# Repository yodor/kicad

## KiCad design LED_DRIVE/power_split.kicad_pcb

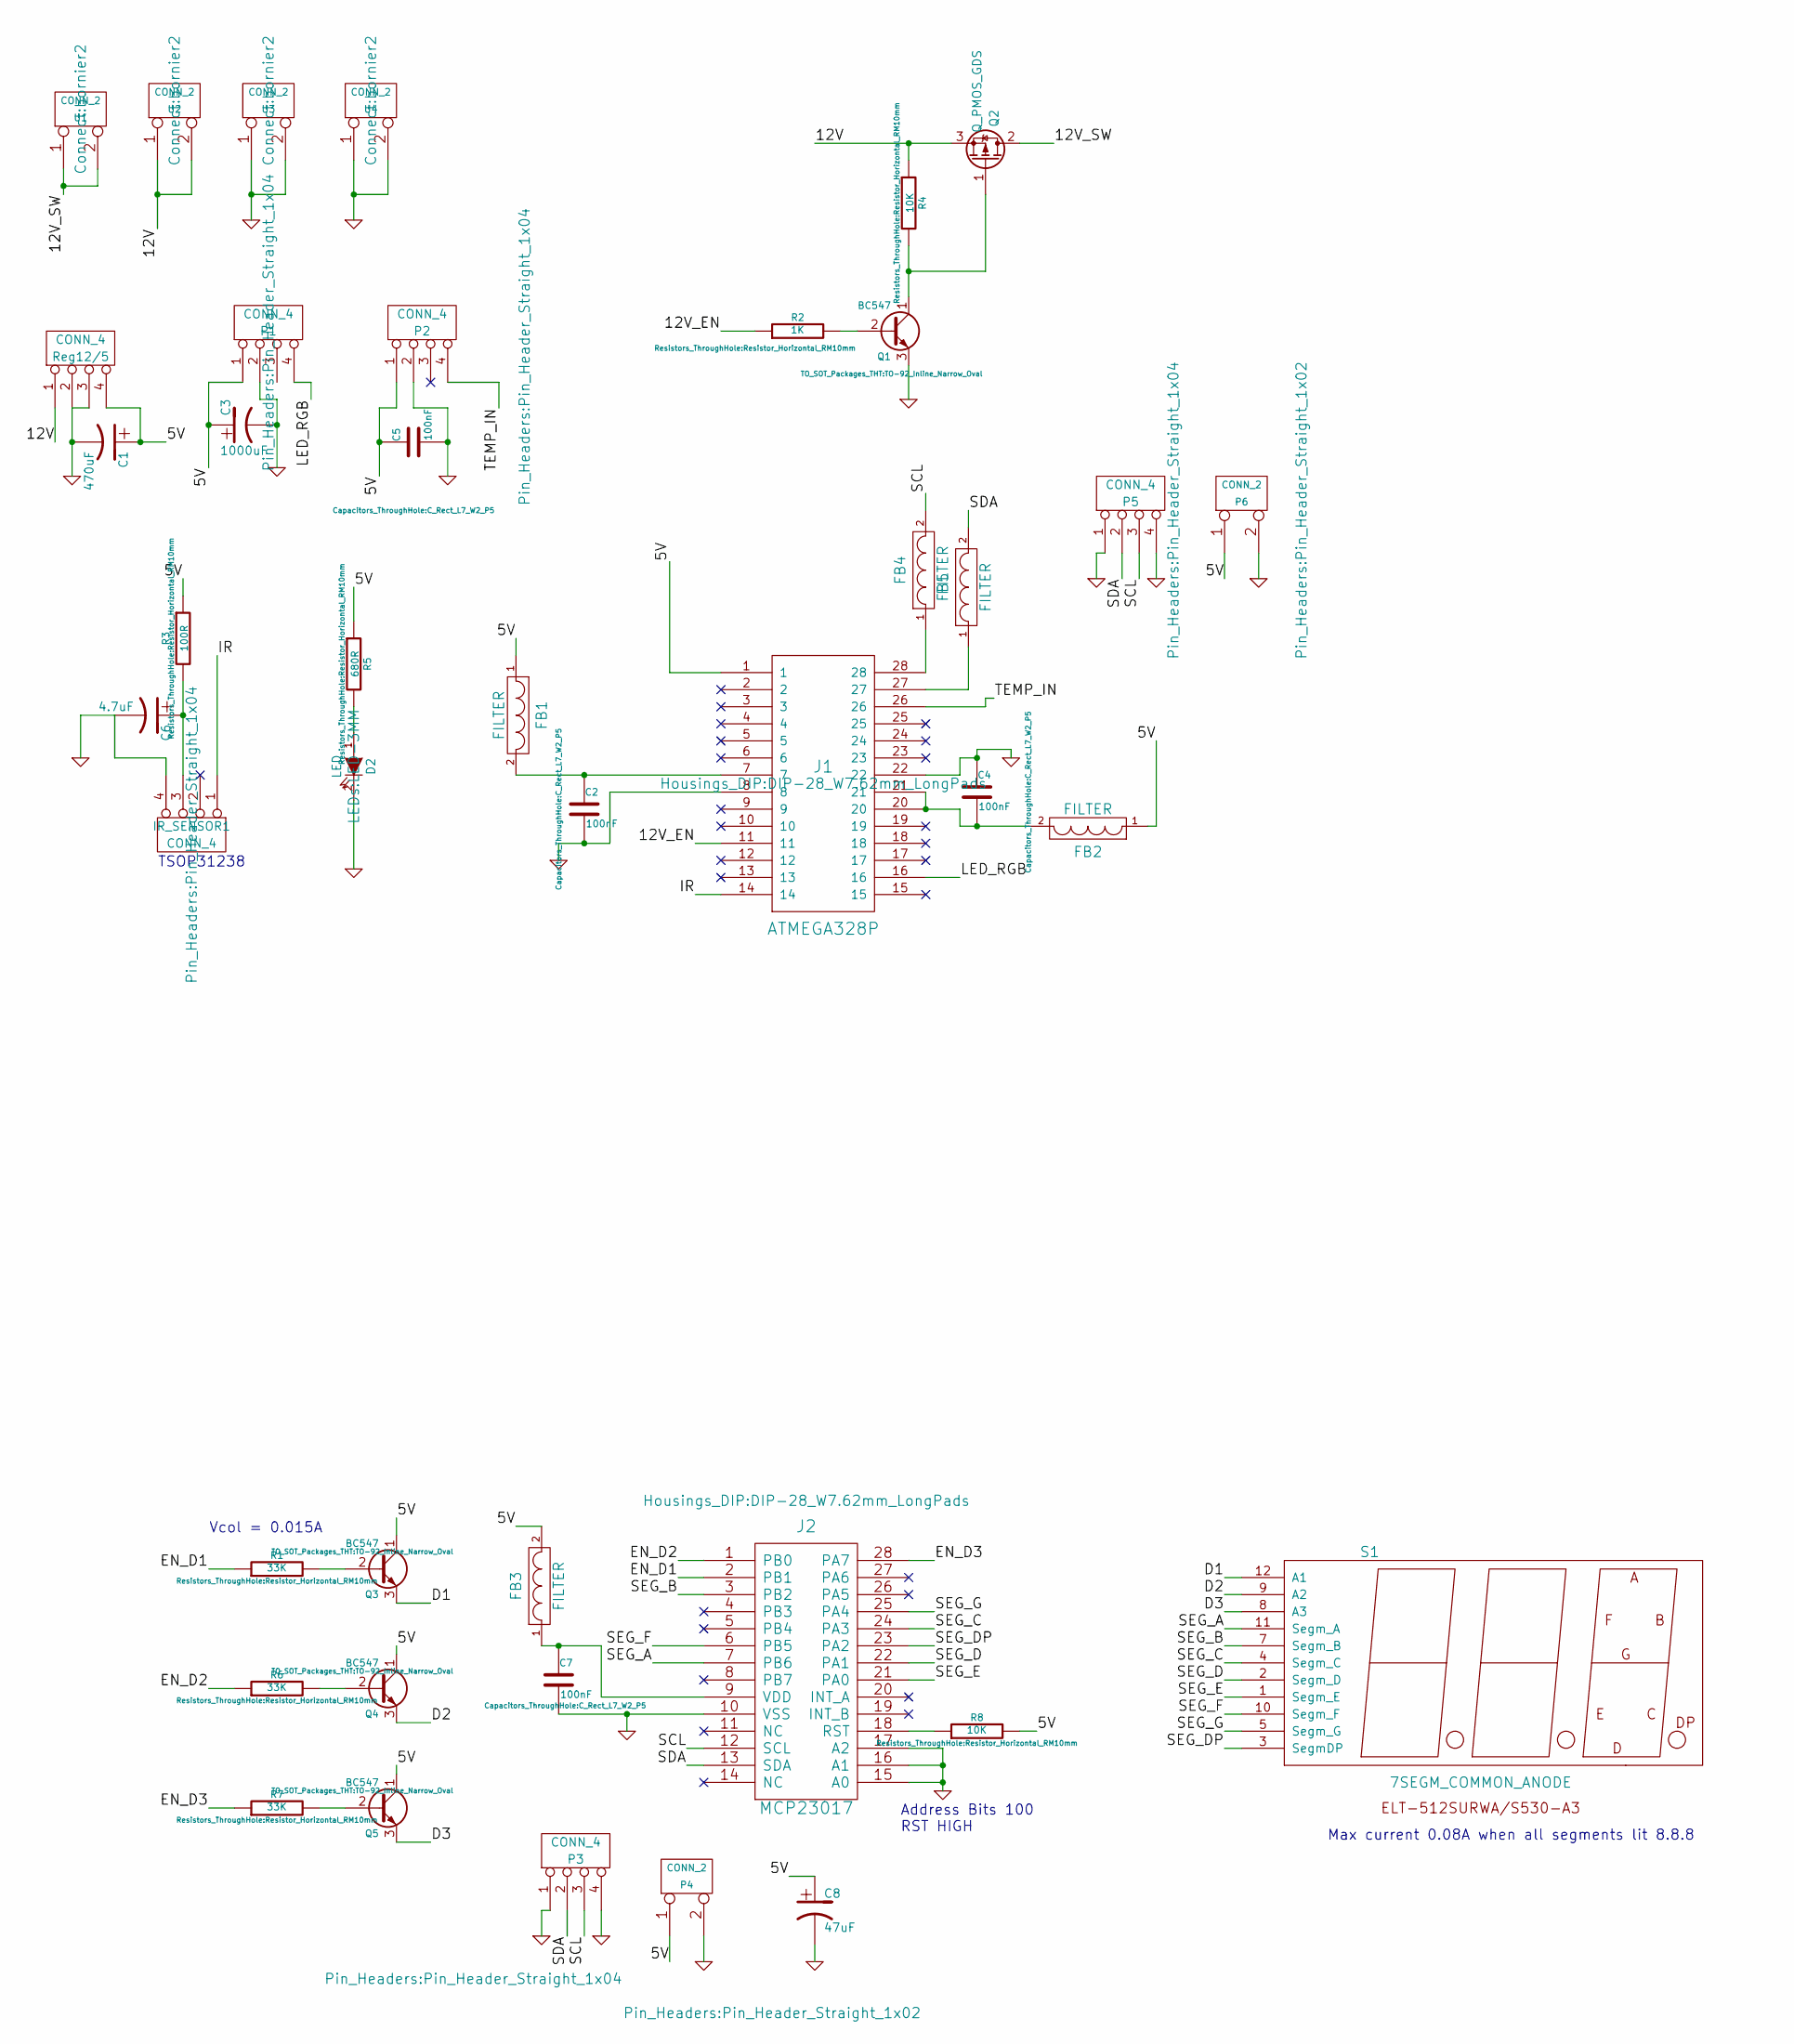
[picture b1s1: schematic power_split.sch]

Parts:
C1: 470uF
C2, C4, C5, C7: 100nF; C_Rect_L7_W2_P5
C3: 1000uF
C6: 4.7uF
C8: 47uF
D2: LED; LED-3MM
FB1, FB2, FB3, FB4, FB5: FILTER; Resistor_Horizontal_RM10mm
IR_SENSOR1: CONN_4; Pin_Header_Straight_1x04
J1: ATMEGA328P; DIP-28_W7.62mm_LongPads
J2: MCP23017; DIP-28_W7.62mm_LongPads
P1, P2, P3, P5: CONN_4; Pin_Header_Straight_1x04
P4, P6: CONN_2; Pin_Header_Straight_1x02
Q1, Q3, Q4, Q5: BC547; TO-92_Inline_Narrow_Oval
Q2: Q_PMOS_GDS; TO-220_Neutral123_Vertical_LargePads
R1, R6, R7: 33K; Resistor_Horizontal_RM10mm
R2: 1K; Resistor_Horizontal_RM10mm
R3: 100R; Resistor_Horizontal_RM10mm
R4, R8: 10K; Resistor_Horizontal_RM10mm
R5: 680R; Resistor_Horizontal_RM10mm
Reg12/5: CONN_4; Pin_Header_Straight_1x04
S1: 7SEGM_COMMON_ANODE; 7segment_common_anode
U1, U2, U3, U4: CONN_2; bornier2

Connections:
/5V: C1.1, C3.1, C5.1, C8.1, FB1.1, FB2.1, FB3.2, J1.1, P1.1, P2.1, P4.1, P6.1, Q3.1 (C), Q4.1 (C), Q5.1 (C), R3.1, R5.1, R8.2, Reg12/5.4
/12V: Q2.3 (S), R4.1, Reg12/5.1, U2.1, U2.2 (PM)
/12V_EN: J1.11, R2.1
/12V_SW: Q2.2 (D), U1.1, U1.2 (PM)
/D1: Q3.3 (E), S1.12 (A1)
/D2: Q4.3 (E), S1.9 (A2)
/D3: Q5.3 (E), S1.8 (A3)
/EN_D1: J2.2 (PB1), R1.1
/EN_D2: J2.1 (PB0), R6.1
/EN_D3: J2.28 (PA7), R7.1
/IR: IR_SENSOR1.1, J1.14
/LED_RGB: J1.16, P1.4
/SCL: FB4.2, J2.12 (SCL), P3.3, P5.3
/SDA: FB5.2, J2.13 (SDA), P3.2, P5.2
/SEG_A: J2.7 (PB6), S1.11 (Segm_A)
/SEG_B: J2.3 (PB2), S1.7 (Segm_B)
/SEG_C: J2.24 (PA3), S1.4 (Segm_C)
/SEG_D: J2.22 (PA1), S1.2 (Segm_D)
/SEG_DP: J2.23 (PA2), S1.3 (SegmDP)
/SEG_E: J2.21 (PA0), S1.1 (Segm_E)
/SEG_F: J2.6 (PB5), S1.10 (Segm_F)
/SEG_G: J2.25 (PA4), S1.5 (Segm_G)
/TEMP_IN: J1.26, P2.4
GND: C1.2, C2.2, C3.2, C4.1, C5.2, C6.2, C7.2, C8.2, D2.2 (K), IR_SENSOR1.4, J1.8, J1.22, J2.10 (VSS), J2.15 (A0), J2.16 (A1), J2.17 (A2), P1.2, P2.2, P3.1, P3.4, P4.2 (PM), P5.1, P5.4, P6.2 (PM), Q1.3 (E), Reg12/5.2, Reg12/5.3, U3.1, U3.2 (PM), U4.1, U4.2 (PM)
unnamed: C2.1, FB1.2, J1.7
unnamed: C4.2, FB2.2, J1.20, J1.21
unnamed: C6.1, IR_SENSOR1.3, R3.2
unnamed: C7.1, FB3.1, J2.9 (VDD)
unnamed: D2.1 (A), R5.2
unnamed: FB4.1, J1.28
unnamed: FB5.1, J1.27
unnamed: J2.18 (RST), R8.1
unnamed: Q1.1 (C), Q2.1 (G), R4.2
unnamed: Q1.2 (B), R2.2
unnamed: Q3.2 (B), R1.2
unnamed: Q4.2 (B), R6.2
unnamed: Q5.2 (B), R7.2

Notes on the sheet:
TSOP31238
Max current 0.08A when all segments lit 8.8.8
Address Bits 100 RST HIGH
Vcol = 0.015A

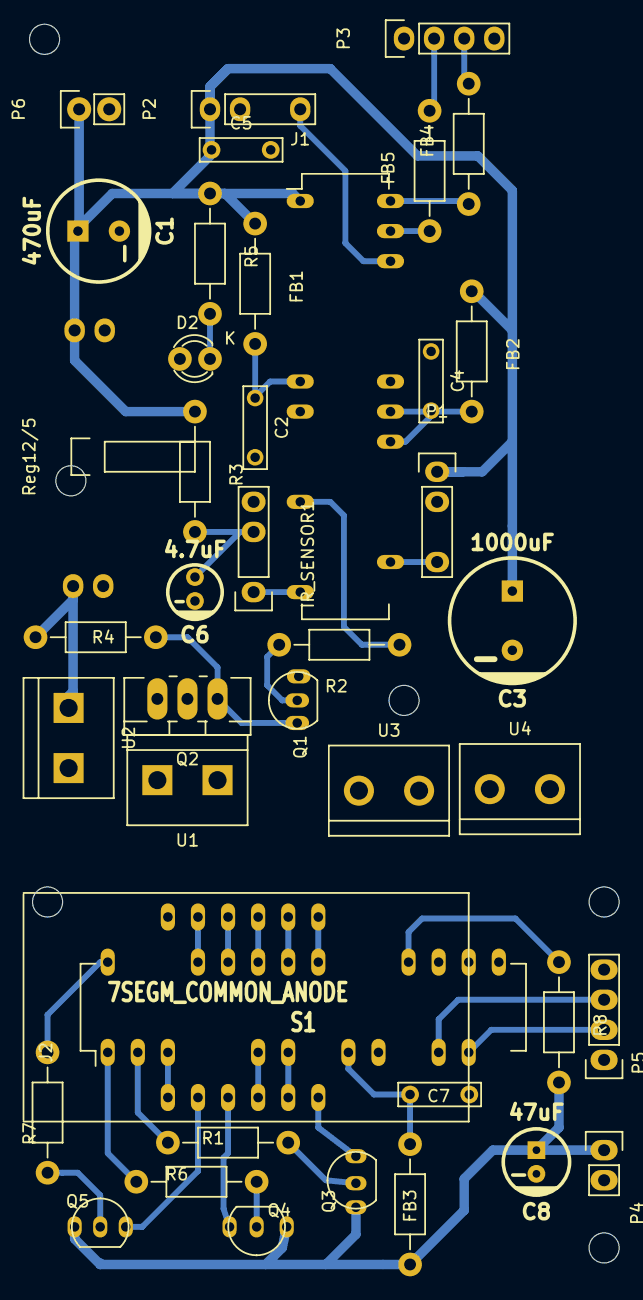
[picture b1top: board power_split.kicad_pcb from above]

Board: 2 copper layers, 49.8 x 104.6 mm, 42 parts (0 on the bottom side), 37 nets.

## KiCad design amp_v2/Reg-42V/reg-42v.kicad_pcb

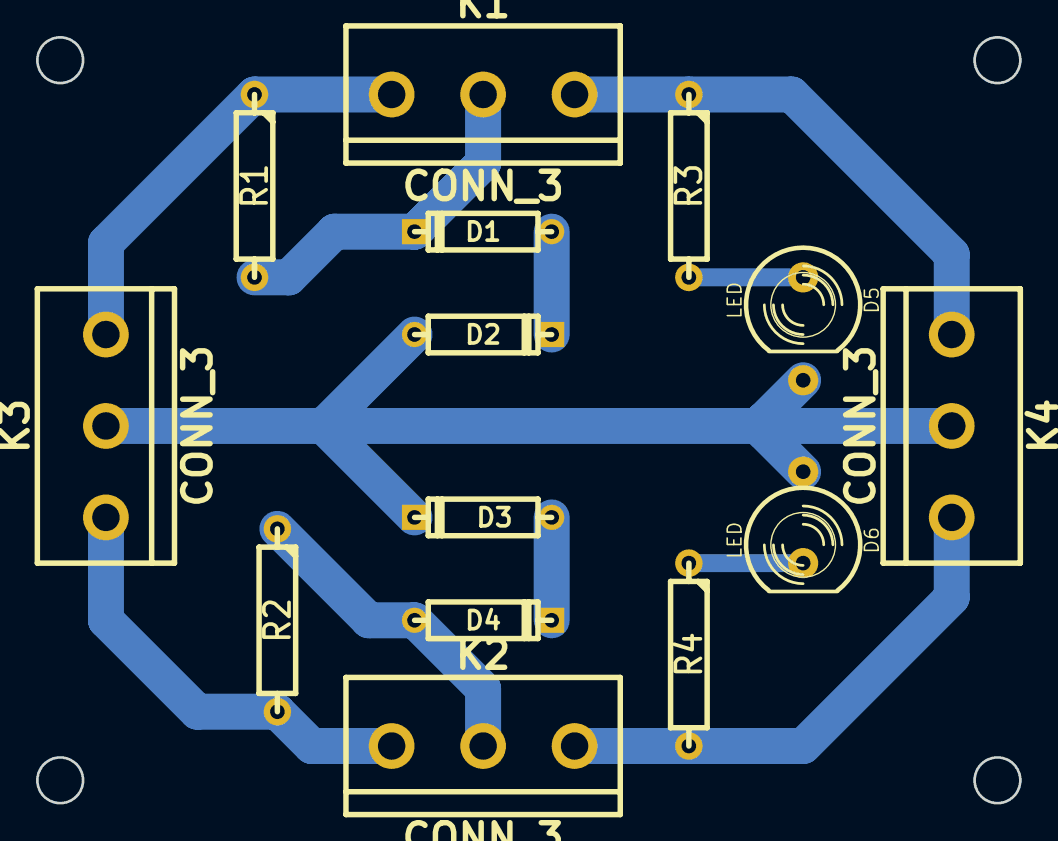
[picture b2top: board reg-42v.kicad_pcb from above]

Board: 2 copper layers, 54.6 x 42.5 mm, 14 parts (0 on the bottom side), 11 nets.

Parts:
D1, D2, D3, D4: ZENER; D3
D5, D6: LED; LED-5MM
K1, K2, K3, K4: CONN_3; bornier3
R1, R2, R3, R4: R; R4

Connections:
/+45: K1.1, K3.3, R1.1
/-45: K2.1, K3.1, R2.2
/N_B: D1.2, K1.2, R1.2
/N_E: K1.3, K4.1, R3.1
/P_B: D4.1, K2.2, R2.1
/P_E: K2.3, K4.3, R4.2
GND: D2.1, D3.2, D5.2, D6.1, K3.2, K4.2
unnamed: D6.2, R4.1
unnamed: D5.1, R3.2
unnamed: D3.1, D4.2
unnamed: D1.1, D2.2

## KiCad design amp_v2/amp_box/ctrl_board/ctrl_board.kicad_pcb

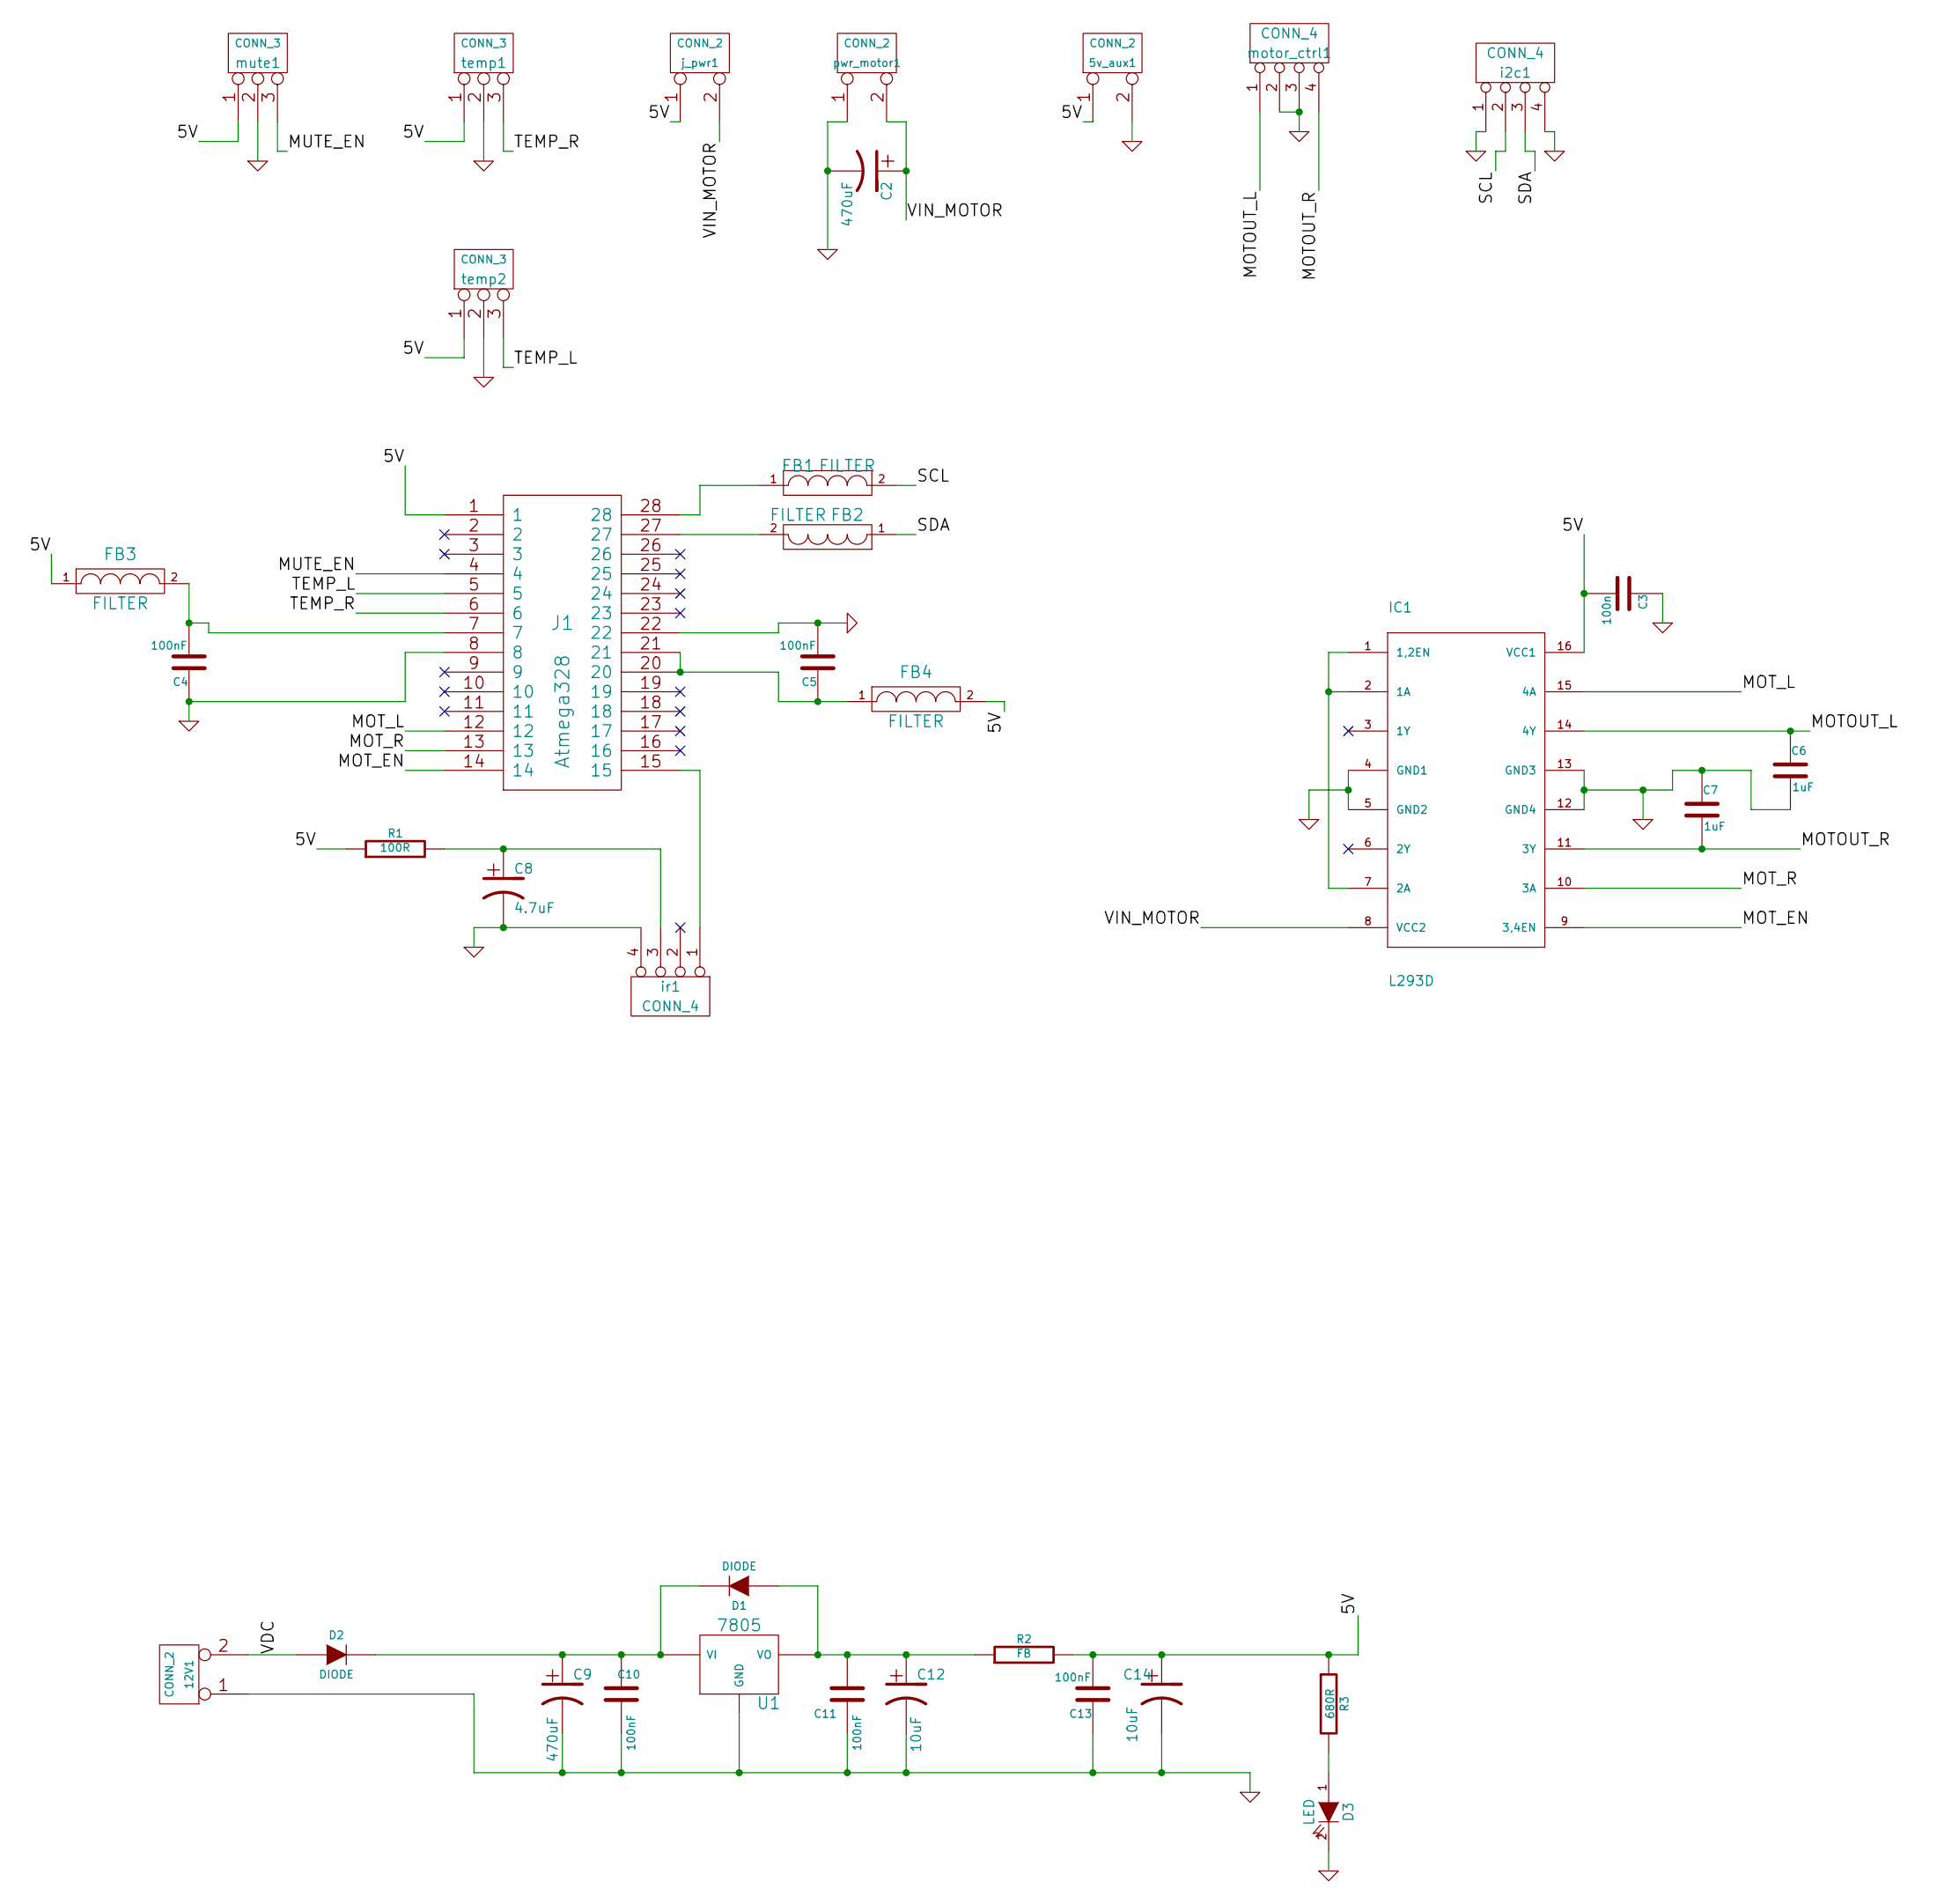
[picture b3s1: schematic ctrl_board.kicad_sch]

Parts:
5v_aux1, 12V1: CONN_2
C2, C9: 470uF
C3: 100n
C4, C5, C10, C11, C13: 100nF
C6, C7: 1uF
C8: 4.7uF
C12, C14: 10uF
D1, D2: DIODE
D3: LED
FB1, FB2, FB3, FB4: FILTER
IC1: L293D; stepper drivers-DIL16
J1: Atmega328
R1: 100R
R2: FB
R3: 680R
U1: 7805
i2c1: CONN_4
ir1: CONN_4
j_pwr1: CONN_2
motor_ctrl1: CONN_4
mute1: CONN_3
pwr_motor1: CONN_2
temp1, temp2: CONN_3

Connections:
/5V: 5v_aux1.1, C3.2, C13.2, C14.1, FB3.1, FB4.2, IC1.16 (VCC1), J1.1, R1.1, R2.2, R3.1, j_pwr1.1, mute1.1, temp1.1, temp2.1
/MOTOUT_L: C6.1, IC1.14 (4Y), motor_ctrl1.1
/MOTOUT_R: C7.2, IC1.11 (3Y), motor_ctrl1.4
/MOT_EN: IC1.9 (3,4EN), J1.14
/MOT_L: IC1.15 (4A), J1.12
/MOT_R: IC1.10 (3A), J1.13
/MUTE_EN: J1.4, mute1.3
/SCL: FB1.2, i2c1.2
/SDA: FB2.1, i2c1.3
/TEMP_L: J1.5, temp2.3
/TEMP_R: J1.6, temp1.3
/VDC: 12V1.2 (PM), D2.1 (A)
/VIN_MOTOR: C2.1, IC1.8 (VCC2), j_pwr1.2 (PM), pwr_motor1.2 (PM)
unnamed: FB1.1, J1.28
unnamed: FB2.2, J1.27
unnamed: J1.15, ir1.1
unnamed: D3.1 (A), R3.2
unnamed: C8.1, R1.2, ir1.3
unnamed: C4.2, FB3.2, J1.7
unnamed: C5.1, FB4.1, J1.20, J1.21
unnamed: C9.1, C10.2, D1.2 (K), D2.2 (K), U1.VI
unnamed: C11.2, C12.1, D1.1 (A), R2.1, U1.VO

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
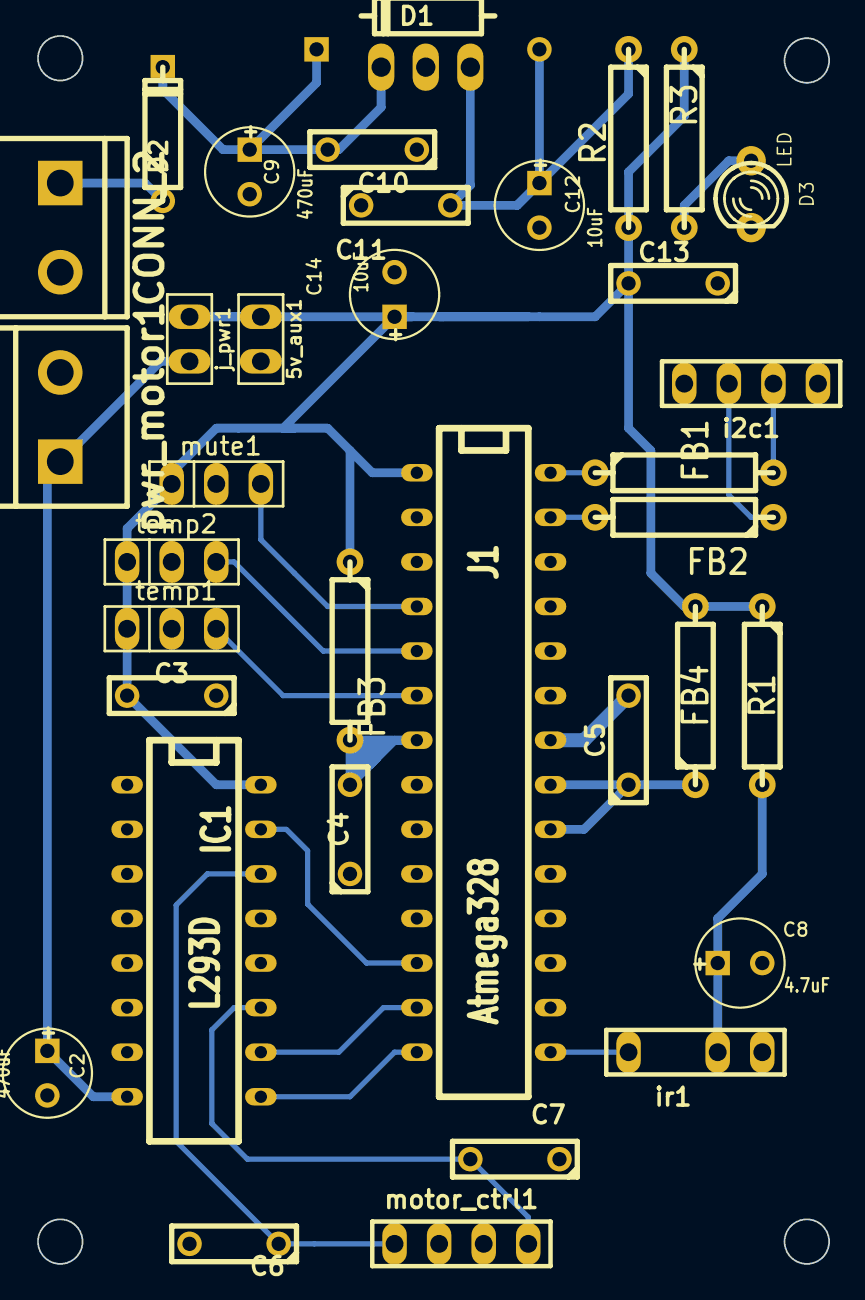
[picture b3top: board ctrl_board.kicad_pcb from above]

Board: 2 copper layers, 45.1 x 70.0 mm, 36 parts (0 on the bottom side), 23 nets.

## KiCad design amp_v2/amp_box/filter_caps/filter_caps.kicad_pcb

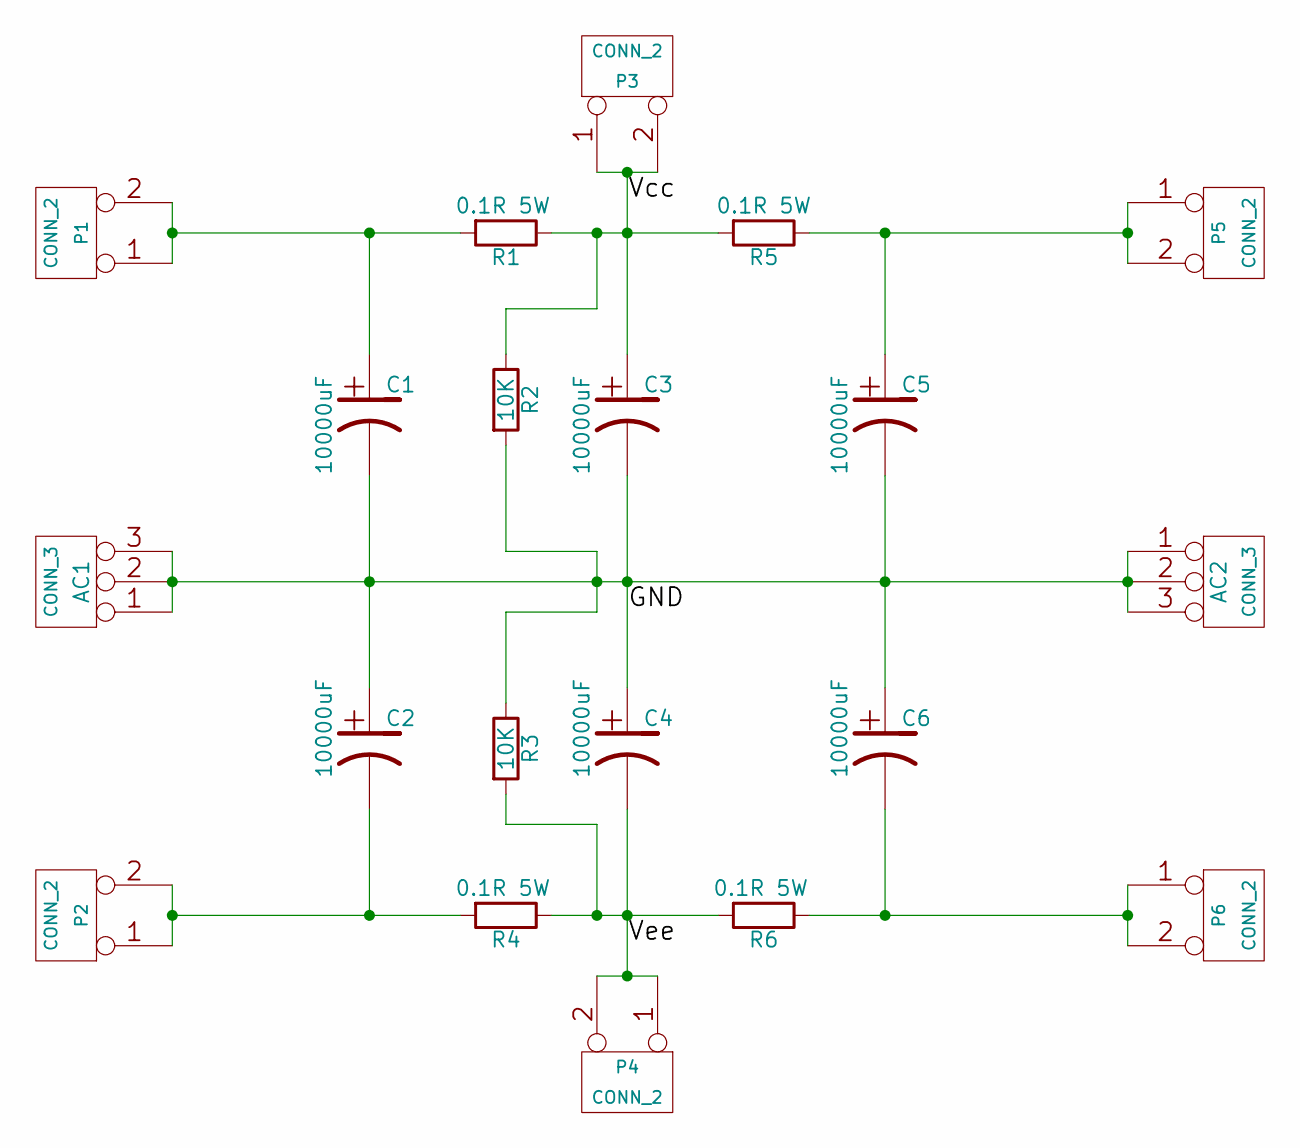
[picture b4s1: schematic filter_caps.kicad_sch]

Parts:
AC1, AC2: CONN_3; bornier3
C1, C2, C3, C4, C5, C6: 10000uF; C_Radial_D30_L51_P10
P1, P2, P3, P4, P5, P6: CONN_2; bornier2
R1, R4, R5, R6: 0.1R 5W; R7
R2, R3: 10K; R4

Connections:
/GND: AC1.1, AC1.2 (PM), AC1.3, AC2.1, AC2.2 (PM), AC2.3, C1.2, C2.1, C3.2, C4.1, C5.2, C6.1, R2.2, R3.1
/Vcc: C3.1, P3.1, P3.2 (PM), R1.1, R2.1, R5.2
/Vee: C4.2, P4.1, P4.2 (PM), R3.2, R4.1, R6.2
unnamed: C1.1, P1.1, P1.2 (PM), R1.2
unnamed: C2.2, P2.1, P2.2 (PM), R4.2
unnamed: C5.1, P5.1, P5.2 (PM), R5.1
unnamed: C6.2, P6.1, P6.2 (PM), R6.1

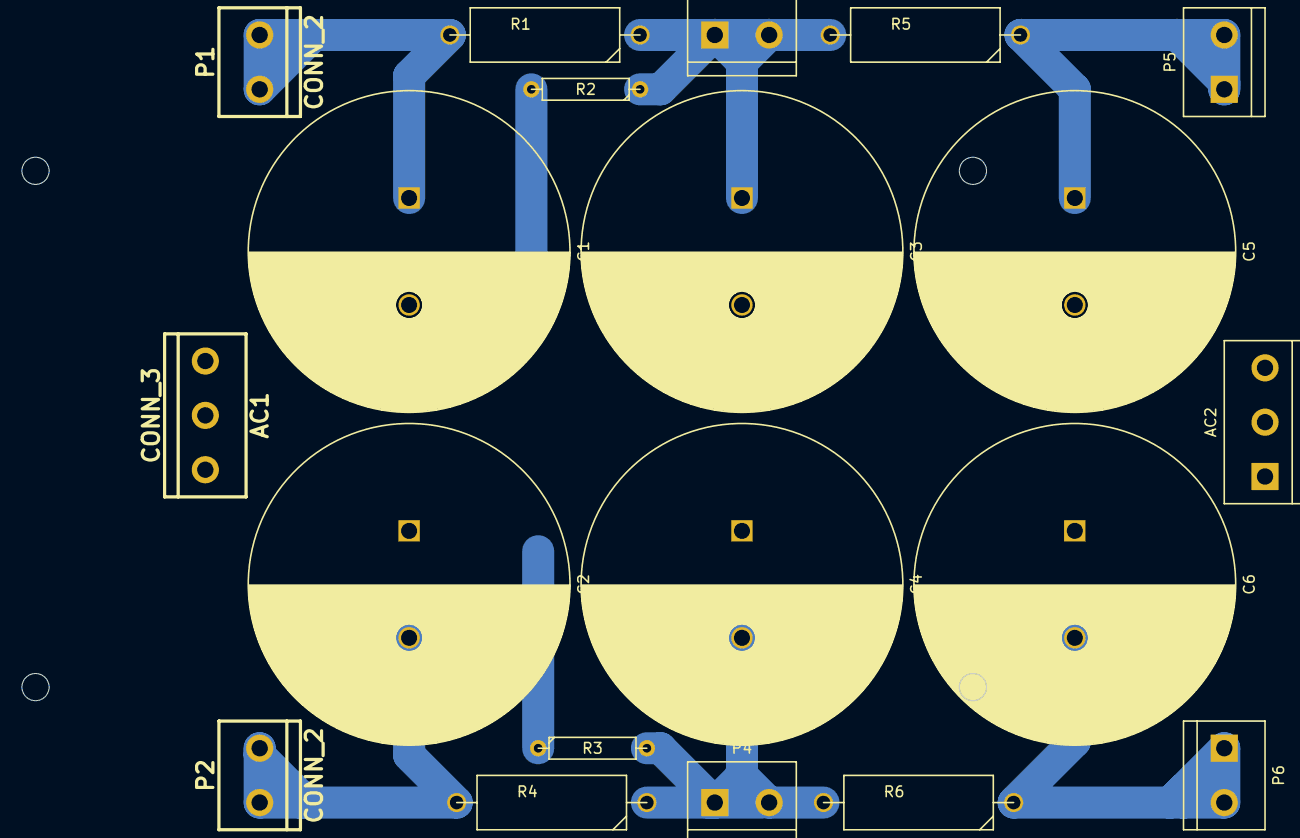
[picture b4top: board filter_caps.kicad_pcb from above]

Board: 2 copper layers, 20 parts (0 on the bottom side), 7 nets.

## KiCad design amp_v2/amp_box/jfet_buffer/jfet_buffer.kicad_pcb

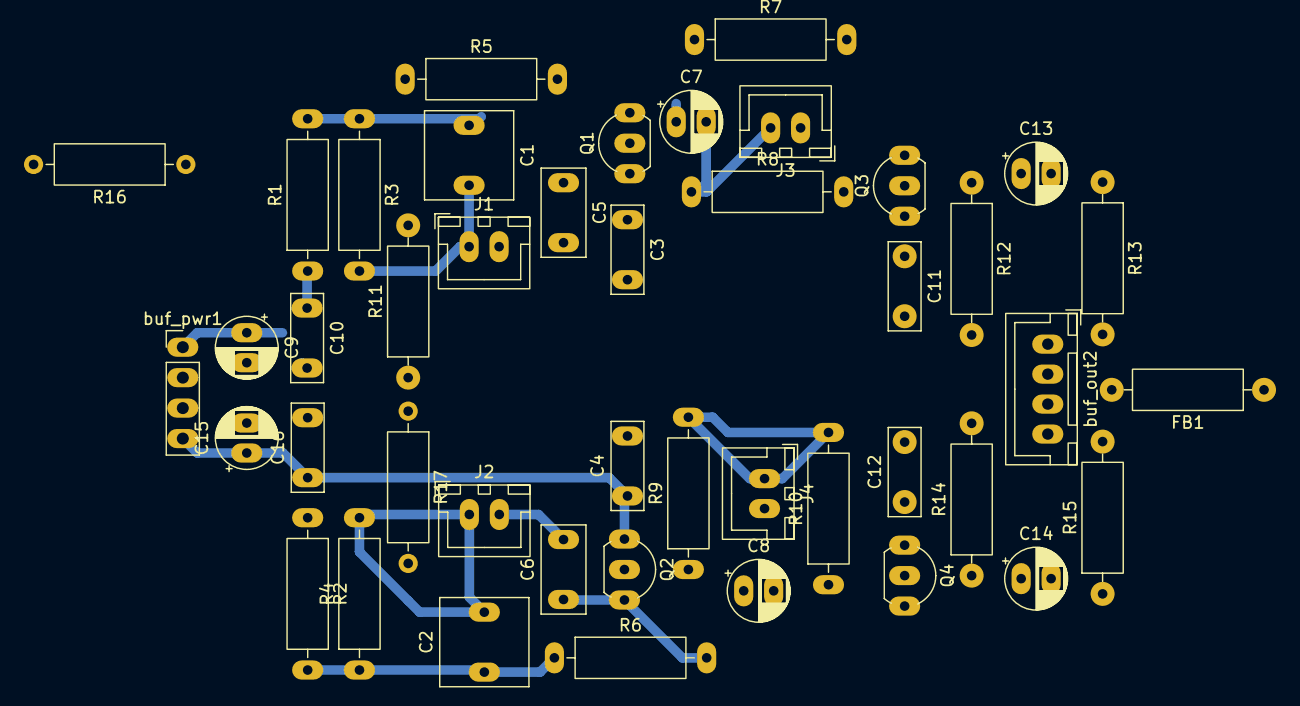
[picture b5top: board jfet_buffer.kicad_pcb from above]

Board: 2 copper layers, 44 parts (0 on the bottom side), 19 nets.

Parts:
C1, C2: 2.2uF; C_Rect_L7.2mm_W7.2mm_P5.00mm_FKS2_FKP2_MKS2_MKP2
C3, C11, C12: 100nF; C_Rect_L7.2mm_W2.5mm_P5.00mm_FKS2_FKP2_MKS2_MKP2
C4, C10, C16: 100nF wima mks2; C_Rect_L7.2mm_W2.5mm_P5.00mm_FKS2_FKP2_MKS2_MKP2
C5, C6: 470nF; C_Rect_L7.2mm_W3.5mm_P5.00mm_FKS2_FKP2_MKS2_MKP2
C7, C8, C13, C14: 4.7uF; CP_Radial_D5.0mm_P2.50mm
C9, C15: 47uF low; CP_Radial_D5.0mm_P2.50mm
FB1: FILTER; R_Axial_DIN0309_L9.0mm_D3.2mm_P12.70mm_Horizontal
J1, J2, J3, J4: Conn_01x02_Pin; JST_XH_B2B-XH-A_1x02_P2.50mm_Vertical
Q1: 2N5457; TO-92L_Inline_Wide
Q2, Q3, Q4: 2N5457 DSG; TO-92L_Inline_Wide
R1, R2, R3, R4, R8, R10, R13, R15: 100K; R_Axial_DIN0309_L9.0mm_D3.2mm_P12.70mm_Horizontal
R5, R6: 1M; R_Axial_DIN0309_L9.0mm_D3.2mm_P12.70mm_Horizontal
R7, R9, R12, R14: 3K; R_Axial_DIN0309_L9.0mm_D3.2mm_P12.70mm_Horizontal
R11, R16, R17: 0R; R_Axial_DIN0309_L9.0mm_D3.2mm_P12.70mm_Horizontal
buf_out2: CONN_4; JST_XH_B4B-XH-A_1x04_P2.50mm_Vertical
buf_pwr1: CONN_4; PinHeader_1x04_P2.54mm_Vertical

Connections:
+9V: C3.1, C4.1, C9.1, C10.1, C11.1, C12.1, C15.1, C16.1, Q1.1 (D), Q2.1 (D), Q3.1 (D), Q4.1 (D), R1.1, R2.1, buf_pwr1.1, buf_pwr1.4
/L_IN: C5.2, J1.2
/L_OUT_BUF1: C7.2, J3.2, R8.1
/L_OUT_BUF2: C13.2, R13.1, buf_out2.1
/R_IN: C6.2, J2.2
/R_OUT_BUF1: C8.2, J4.2, R10.1
/R_OUT_BUF2: C14.2, R15.1, buf_out2.4
/VBIAS_L: C1.1, R1.2, R3.1, R5.1
/VBIAS_R: C2.1, R2.2, R4.1, R6.1
GNDD: FB1.2, R12.2, R13.2, R14.2, R15.2, buf_out2.2, buf_out2.3
GND_IN: C1.2, C2.2, J1.1, J2.1, R3.2, R4.2, R11.2, R17.2
GND_OUT: J3.1, J4.1, R7.2, R8.2, R9.2, R10.2, R16.1
GND_PWR: C3.2, C4.2, C9.2, C10.2, C11.2, C12.2, C15.2, C16.2, R11.1, R16.2, R17.1, buf_pwr1.2, buf_pwr1.3
unnamed: C5.1, Q1.3 (G), Q3.3 (G), R5.2
unnamed: C7.1, Q1.2 (S), R7.1
unnamed: C6.1, Q2.3 (G), Q4.3 (G), R6.2
unnamed: C8.1, Q2.2 (S), R9.1
unnamed: C13.1, Q3.2 (S), R12.1
unnamed: C14.1, Q4.2 (S), R14.1

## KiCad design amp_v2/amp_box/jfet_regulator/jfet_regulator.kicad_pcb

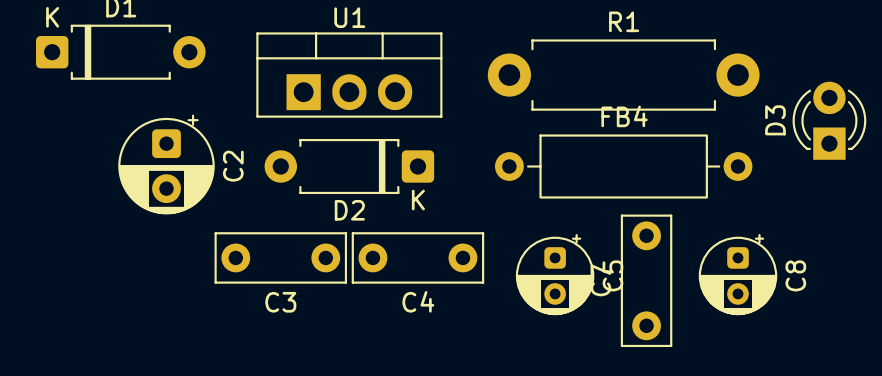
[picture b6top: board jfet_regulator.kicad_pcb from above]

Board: 2 copper layers, 12 parts (0 on the bottom side), 5 nets, no tracks yet.

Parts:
C2: 470uF; CP_Radial_D5.0mm_P2.50mm
C3, C4, C7: 100nF; C_Rect_L7.0mm_W2.5mm_P5.00mm
C5, C8: 10uF; CP_Radial_D4.0mm_P2.00mm
D1, D2: DIODE; D_A-405_P7.62mm_Horizontal
D3: LED; LED_D3.0mm
FB4: FILTER; R_Axial_DIN0309_L9.0mm_D3.2mm_P12.70mm_Horizontal
R1: 680R; R_Axial_DIN0411_L9.9mm_D3.6mm_P12.70mm_Horizontal
U1: 7815; TO-220-3_Vertical

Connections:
/5V: C7.2, C8.1, FB4.2, R1.1
GND: C2.2, C3.1, C4.1, C5.2, C7.1, C8.2
unnamed: C2.1, C3.2, D1.2 (K), D2.2 (K)
unnamed: C4.2, C5.1, D2.1 (A), FB4.1
unnamed: D3.2 (A_2), R1.2

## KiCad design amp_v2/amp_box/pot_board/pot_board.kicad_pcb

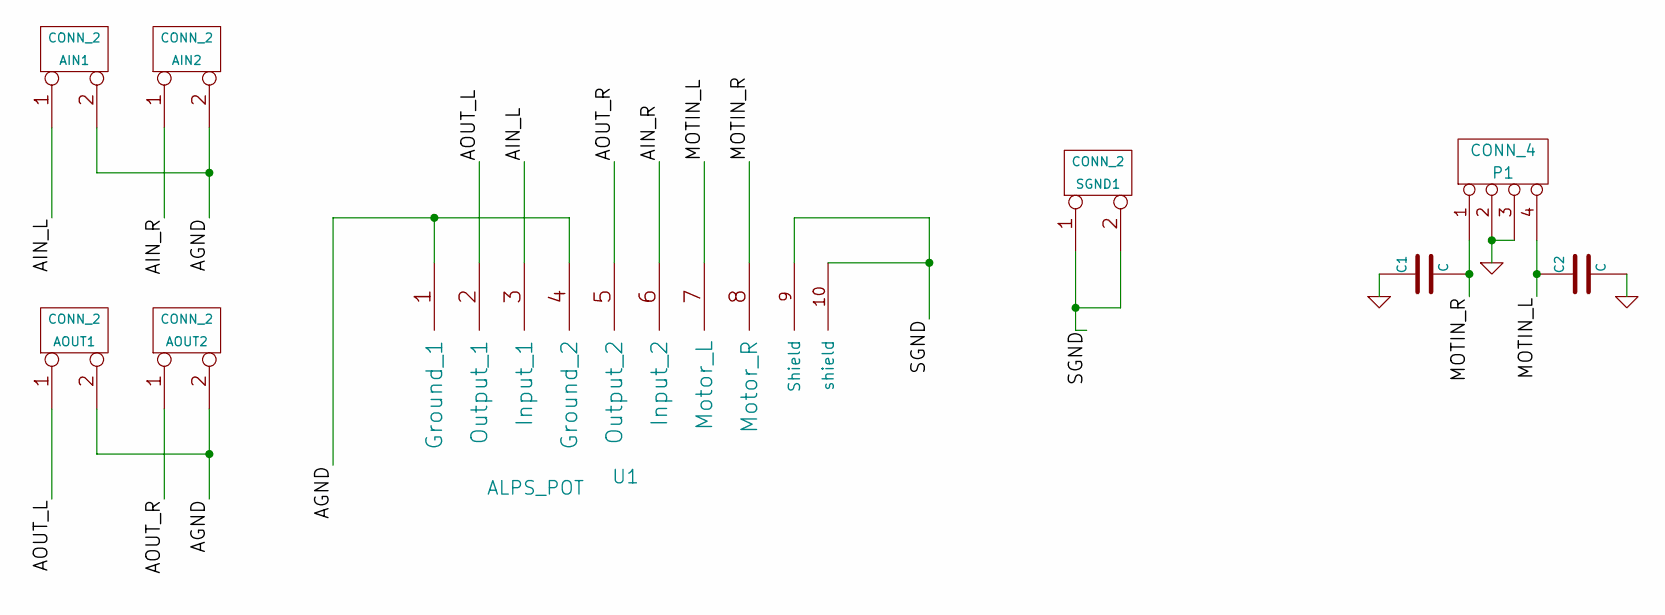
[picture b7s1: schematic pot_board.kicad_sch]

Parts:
AIN1, AIN2: CONN_2
AOUT1, AOUT2: CONN_2
C1, C2: C
P1: CONN_4
SGND1: CONN_2
U1: ALPS_POT

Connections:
/AGND: AIN1.2 (PM), AIN2.2 (PM), AOUT1.2 (PM), AOUT2.2 (PM), U1.1 (Ground_1), U1.4 (Ground_2)
/AIN_L: AIN1.1, U1.3 (Input_1)
/AIN_R: AIN2.1, U1.6 (Input_2)
/AOUT_L: AOUT1.1, U1.2 (Output_1)
/AOUT_R: AOUT2.1, U1.5 (Output_2)
/MOTIN_L: C2.1, P1.4, U1.7 (Motor_L)
/MOTIN_R: C1.2, P1.1, U1.8 (Motor_R)
/SGND: SGND1.1, SGND1.2 (PM), U1.9 (Shield), U1.10 (shield)
GND: C1.1, C2.2, P1.2, P1.3

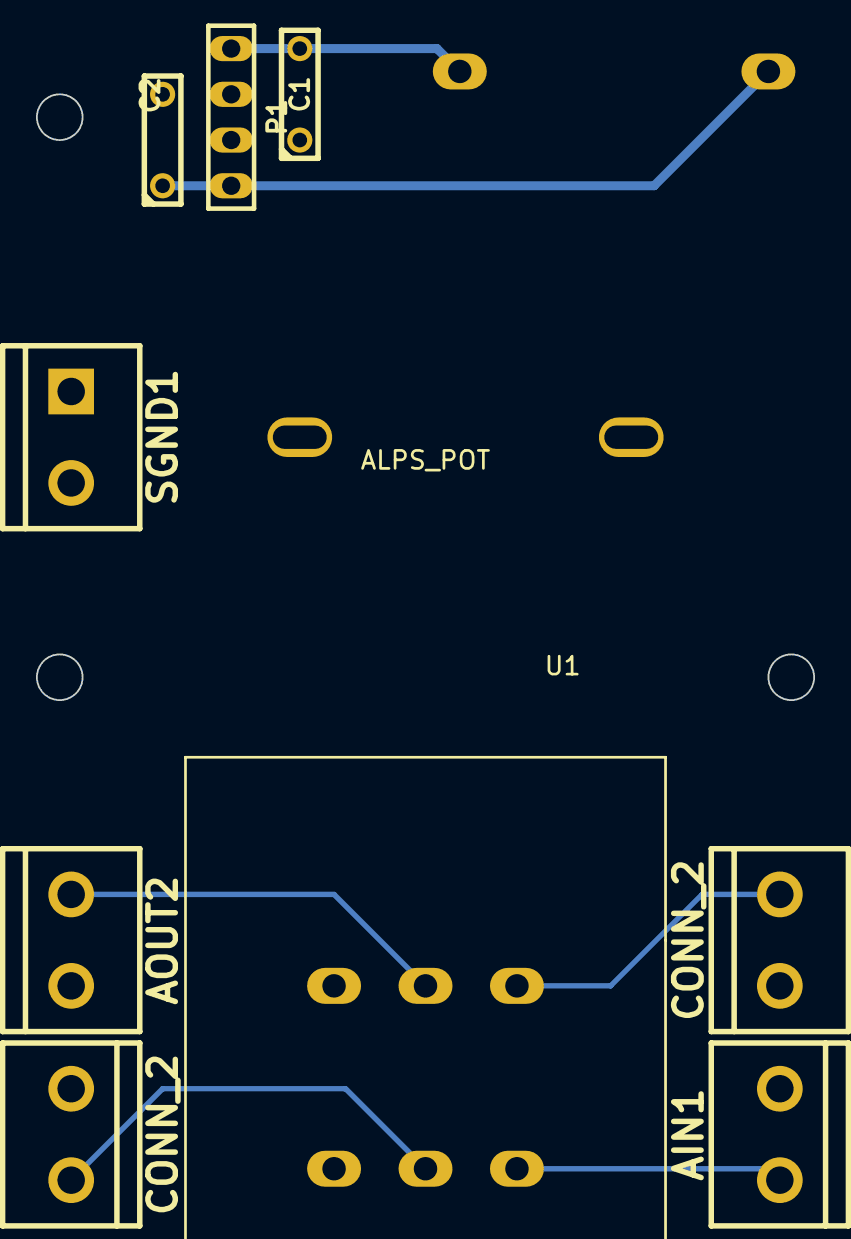
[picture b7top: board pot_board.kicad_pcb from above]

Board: 2 copper layers, 9 parts (0 on the bottom side), 9 nets.
